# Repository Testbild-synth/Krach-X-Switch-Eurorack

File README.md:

# Krach X-Switch Eurorack Performance Module

Recently, I was commissioned by [Krach der Roboter](https://www.facebook.com/KrachDerRoboter/) who had the idea to design a passive performance tool based on the idea of quickly switching signal paths. What came out of it is this simple and useful module:

## Status: recently added version 1.3 which has improved spacing for cut/connect switch legs

## Function

The core function of the module revolves around the "cross-switch". Two input channels are attenuated independently and then go to the output, but if you flip the cross switch, the Input 1 goes into output 2 and vice versa. This allows for fast back and forth switching of cv signals.
Additional pushbuttons can be used to cut or connect a lane. Spacing between components is rather large to allow his robot hands to reach everything easily.

This is also meant as an absolute beginner/first DIY module, so everything is made to be very easy to solder and all the traces are rather large so nothing gets damaged.

## PCB and Hardware

You can find the schematic and BOM in the root folder.
For the PCBs, the module has one circuit PCB and one panel PCB. 
You can order them on any common PCB manufacturing service, we used [JLCPCB](https://jlcpcb.com/).

Standard settings should be fine, but as there is exposed copper on the panel you should go with a lead free surface finish (ENIG/Leadfree HASL).
If the panel sizes are not recognized correctly (may happen with my export sometimes) just put 128.5x50mm.

For the push switches, we used these, but you can use any that will somewhat fit the footprint and have <m7 thread on the top.

## Assembly
Should be very straight forward, as always it is best to mount the components on the panel first before soldering so that they are properly in place.

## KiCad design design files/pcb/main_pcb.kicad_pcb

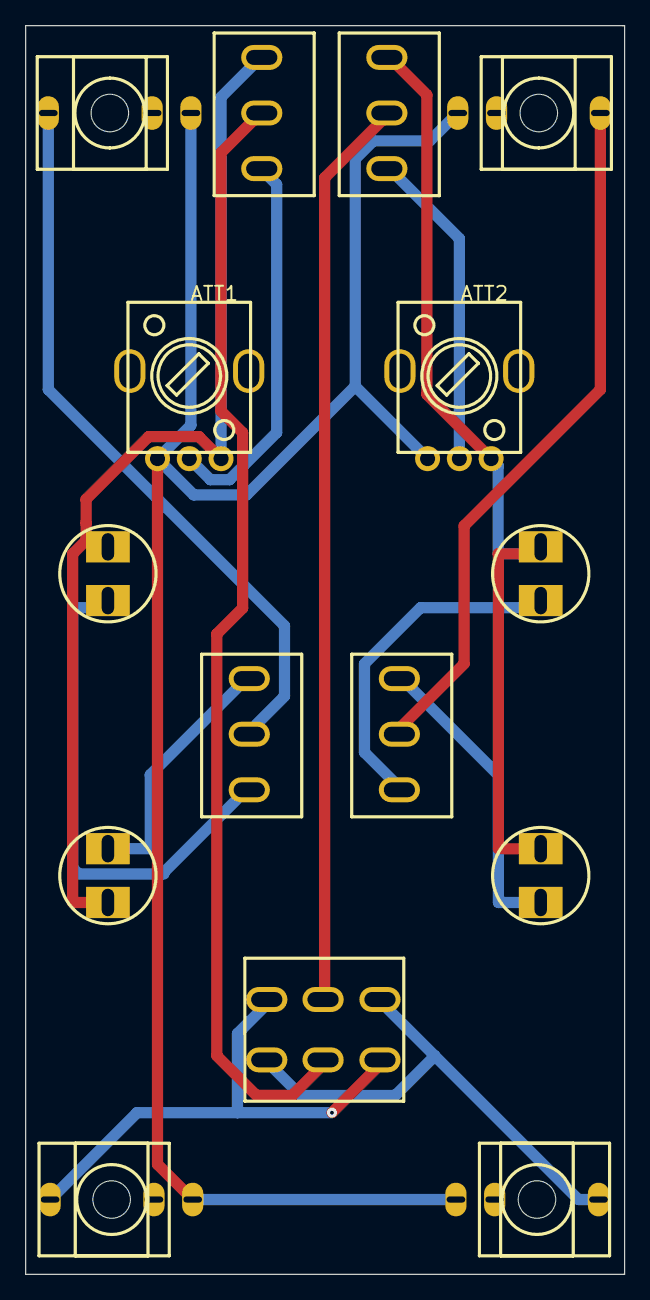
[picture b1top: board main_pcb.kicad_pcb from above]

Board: 2 copper layers, 47.9 x 99.8 mm, 15 parts (0 on the bottom side), 15 nets.

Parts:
ATT1, ATT2: 100k; R09-5KΩ
J1: IN1; THONKICONN_1
J2: IN2; THONKICONN_1
J3: OUT1; THONKICONN_1
J4: OUT2; THONKICONN_1
PB1, PB3: CUT; PUSHBUTTON
PB2, PB4: CONNECT; PUSHBUTTON
SW1: DPDT CROSS; 6 PIN DPDT MOM SWITCH
U1, U4: CUT/CONNECT; MINI TOGGLE SWITCH SPDT ON-ON
U2, U3: ATT BYPASS; MINI TOGGLE SWITCH SPDT ON-ON

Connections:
ATT1_2: ATT1.2, U3.2
ATT2_2: ATT2.2, U2.2
GND: ATT1.1, ATT2.1, J1.1, J2.1, J3.1, J4.1
PB2_2: ATT1.3, PB1.2, PB2.2, U3.3
PB3_1: PB3.1, U1.2
PB3_2: ATT2.3, PB3.2, PB4.2, U2.3
PB4_1: PB4.1, U1.3
SW1_1: J4.3, SW1.1, SW1.6
SW1_2: SW1.2, U3.1
SW1_3: J3.3, SW1.3, SW1.4
SW1_5: SW1.5, U2.1
U1_1: J2.3, U1.1
U4_1: J1.3, U4.1
U4_2: PB1.1, U4.2
U4_3: PB2.1, U4.3

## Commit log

2022-02-17 preliminary readme
2022-02-17 upload gerbers and some design files
2022-06-07 V1.2 small fix to pcb holes
2023-06-06 v1_3 upload, better spacing for cut/connect switches
2023-06-23 v13 with slightly bigger holes
